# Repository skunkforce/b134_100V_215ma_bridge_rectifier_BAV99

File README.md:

# edgy_board number b134
This design is part of the [edgy board project](https://github.com/skunkforce/edgy_boards). 

# getting started
This repository uses submodules. After cloning use the command 

```$ git submodule update --init --recursive```

to pull the submodules before opening the project with kicad. 

# Tests
Tests can be found in [TESTS.md](TESTS.md)

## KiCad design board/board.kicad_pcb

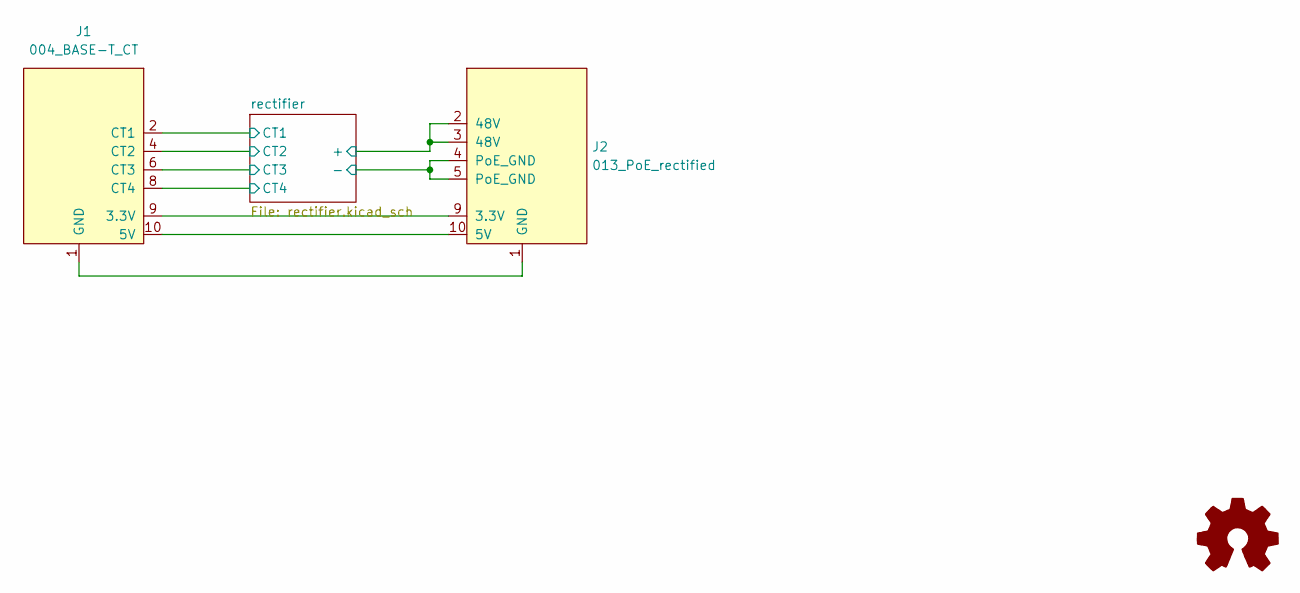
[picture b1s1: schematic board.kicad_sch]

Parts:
J1: 004_BASE-T_CT; on_edge_2x05_device
J2: 013_PoE_rectified; on_edge_2x05_host
LOGO1: Logo_Open_Hardware_Small; OSHW-Symbol_6.7x6mm_SilkScreen

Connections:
/rectifier/+: J2.2 (48V), J2.3 (48V); also elsewhere on the board
/rectifier/-: J2.4 (PoE_GND), J2.5 (PoE_GND); also elsewhere on the board
/rectifier/CT1: J1.2 (CT1); also elsewhere on the board
/rectifier/CT2: J1.4 (CT2); also elsewhere on the board
/rectifier/CT3: J1.6 (CT3); also elsewhere on the board
/rectifier/CT4: J1.8 (CT4); also elsewhere on the board
unnamed: J1.9 (3.3V), J2.9 (3.3V)
unnamed: J1.10 (5V), J2.10 (5V)
unnamed: J1.1 (GND), J2.1 (GND)

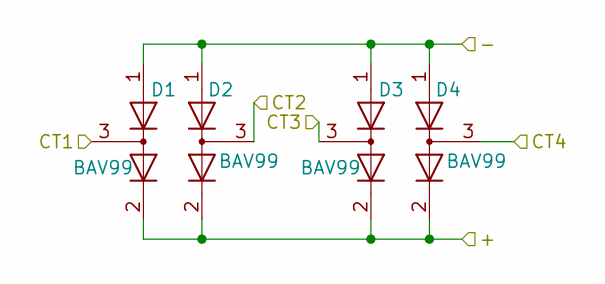
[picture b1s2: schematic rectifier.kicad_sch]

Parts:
D1, D2, D3, D4: BAV99; SOT-23

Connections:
/rectifier/+: D1.2 (A), D2.2 (A), D3.2 (A), D4.2 (A); also elsewhere on the board
/rectifier/-: D1.1 (K), D2.1 (K), D3.1 (K), D4.1 (K); also elsewhere on the board
/rectifier/CT1: D1.3 (K); also elsewhere on the board
/rectifier/CT2: D2.3 (K); also elsewhere on the board
/rectifier/CT3: D3.3 (K); also elsewhere on the board
/rectifier/CT4: D4.3 (K); also elsewhere on the board

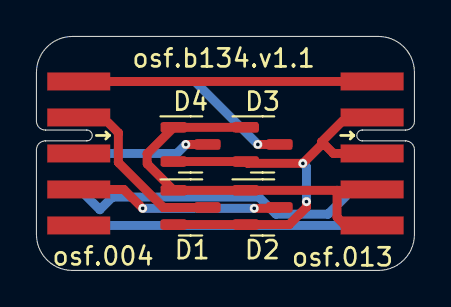
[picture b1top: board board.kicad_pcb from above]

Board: 2 copper layers, 21.0 x 13.0 mm, 7 parts (1 on the bottom side), 9 nets.

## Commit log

2023-05-24 initial
2023-12-22 fixed reverse polarity bug
